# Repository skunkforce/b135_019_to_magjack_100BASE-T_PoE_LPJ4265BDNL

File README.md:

# edgy_board number b135
This design is part of the [edgy board project](https://github.com/skunkforce/edgy_boards). It provides a 100BASE-T PoE capable magjack with internal cable side termination but no internal rectifier. [View in browser with kiCanvas](https://kicanvas.org/?github=https://github.com/skunkforce/b135_019_to_magjack_100BASE-T_PoE_LPJ4265BDNL/tree/master/board).

# getting started
This repository uses submodules. After cloning use the command 

```$ git submodule update --init --recursive```

to pull the submodules before opening the project with kicad. 

# Tests
Tests can be found in [TESTS.md](TESTS.md)

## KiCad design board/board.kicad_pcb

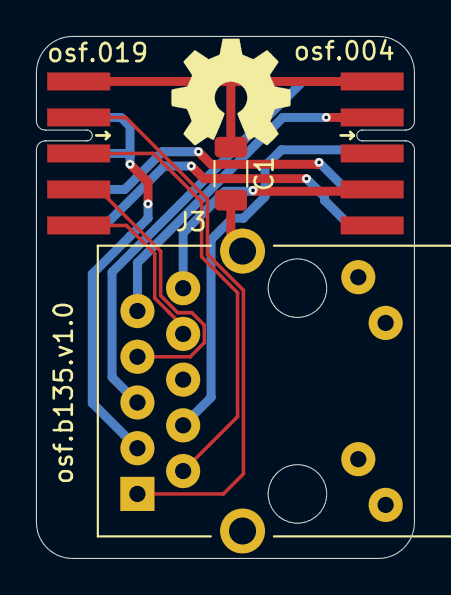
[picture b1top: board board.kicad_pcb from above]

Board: 2 copper layers, 21.0 x 29.0 mm, 5 parts (0 on the bottom side), 13 nets.

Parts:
C1: d.n.p; C_1206_3216Metric
J1: 019_100BASE-T_with_CT; on_edge_2x05_device
J2: 004_BASE-T_CT; on_edge_2x05_host
J3: LPJ4265BDNL
LOGO1: Logo_Open_Hardware_Small; OSHW-Symbol_6.7x6mm_SilkScreen

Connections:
/magjack/CT: J1.7 (CT1), J1.8 (CT2), J3.3 (CT)
/magjack/CT1: J2.2 (CT1), J3.9
/magjack/CT2: J2.4 (CT2), J3.10
/magjack/CT3: J2.6 (CT3), J3.5
/magjack/CT4: J2.8 (CT4), J3.4
/magjack/RX+: J1.4 (TD2+), J3.7 (RD+)
/magjack/RX-: J1.5 (TD2-), J3.8 (RD-)
/magjack/SH: C1.2, J3.SH
/magjack/TX+: J1.2 (TD1+), J3.1 (TD+)
/magjack/TX-: J1.3 (TD1-), J3.2 (TD-)
unnamed: C1.1, J1.1 (GND), J1.6 (GND), J2.1 (GND)
unnamed: J1.9 (3.3V), J2.9 (3.3V)
unnamed: J1.10 (5V), J2.10 (5V)

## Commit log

2023-05-27 initial
2024-01-30 added kicanvas link to README.md
2024-01-30 updated to kicad 7
